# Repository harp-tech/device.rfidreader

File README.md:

# Harp RFID reader

RFID reader for 125KHz carriers.
Compible with glass capsules, buttons and cards (check pics folder).

# Licensing

The code, designs, documentation, and photos available in this repository is free: you can redistribute it and/or modify it under the terms of the used license.
Each subdirectory will contain a license or, possibly, a set of licenses if it involves both hardware and software. Check files named LICENSE.

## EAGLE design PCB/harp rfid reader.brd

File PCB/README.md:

# Harp RFID reader

## Licensing

The designs, documentation, and photos available in this repository are free: you can redistribute it and/or modify it under the terms of the used license.
Check file named LICENSE.

Copyright Filipe Carvalho 2021-2022

<br />This work is licensed under a <a rel="license" href="http://creativecommons.org/licenses/by-nc-sa/3.0/igo/">Creative Commons Attribution-NonCommercial-ShareAlike 3.0 IGO License</a>.

If your are interested in obtaining a license to sell this device, please contact filipe@open-ephys.org

[1]: https://docs.google.com/spreadsheets/d/1aobmmEzBDethzIlrm1eg0eYkBqlyX3s9WbA9KgRwVQI/edit?usp=sharing

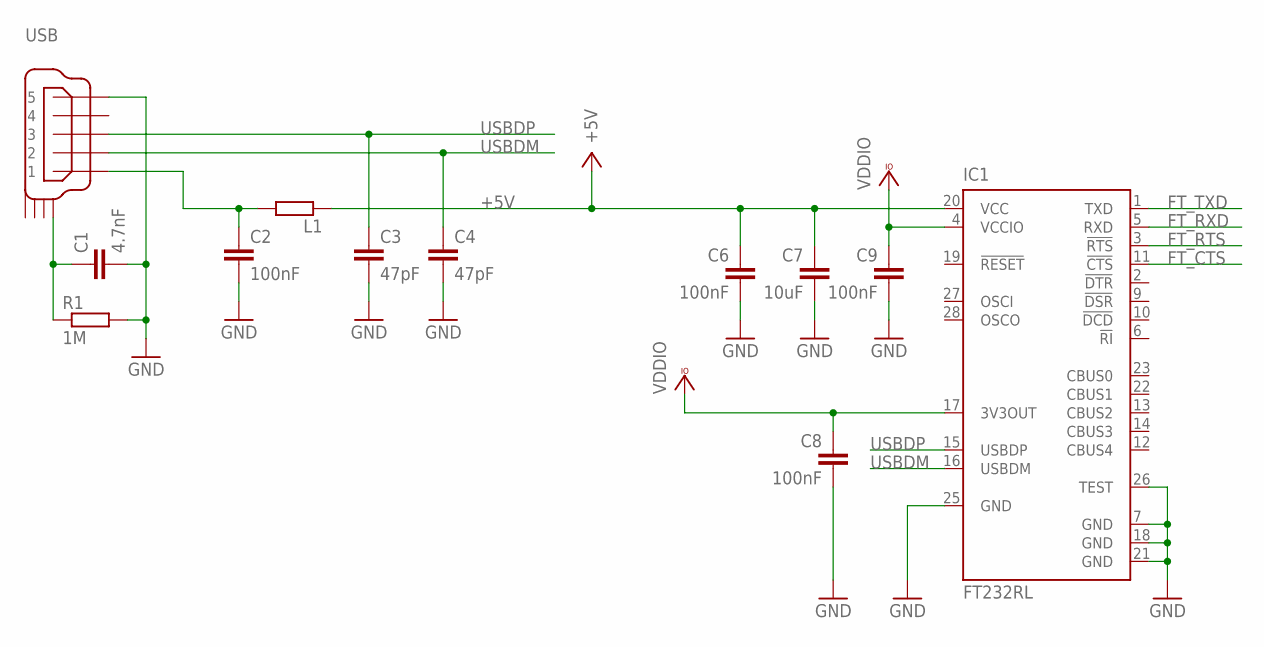
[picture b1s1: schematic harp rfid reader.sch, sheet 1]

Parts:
C1: 4.7nF; C0402
C2, C6, C8, C9: 100nF; C0402
C3, C4: 47pF; C0402
C7: 10uF; C0603
IC1: FT232RL; SSOP28
L1: ???; R0805
R1: 1M; R0402
USB: USB_MINI_B; 240-0002-1

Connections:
+5V: C6.1, C7.1, IC1.20 (VCC), L1.1; also elsewhere on the board
FT_CTS: IC1.11 (!CTS); also elsewhere on the board
FT_RTS: IC1.3 (!RTS); also elsewhere on the board
FT_RXD: IC1.5 (RXD); also elsewhere on the board
FT_TXD: IC1.1 (TXD); also elsewhere on the board
GND: C1.2, C2.2, C3.2, C4.2, C6.2, C7.2, C8.2, C9.2, IC1.7 (GND), IC1.18 (GND), IC1.21 (GND), IC1.25 (GND), IC1.26 (TEST), R1.2, USB.P$5 (5); also elsewhere on the board
unnamed: C1.1, R1.1, USB.SHIELD_1
unnamed: C2.1, L1.2, USB.P$1 (1)
USBDM: C4.1, IC1.16 (USBDM), USB.P$2 (2)
USBDP: C3.1, IC1.15 (USBDP), USB.P$3 (3)
VCCIO: C8.1, C9.1, IC1.4 (VCCIO), IC1.17 (3V3OUT); also elsewhere on the board

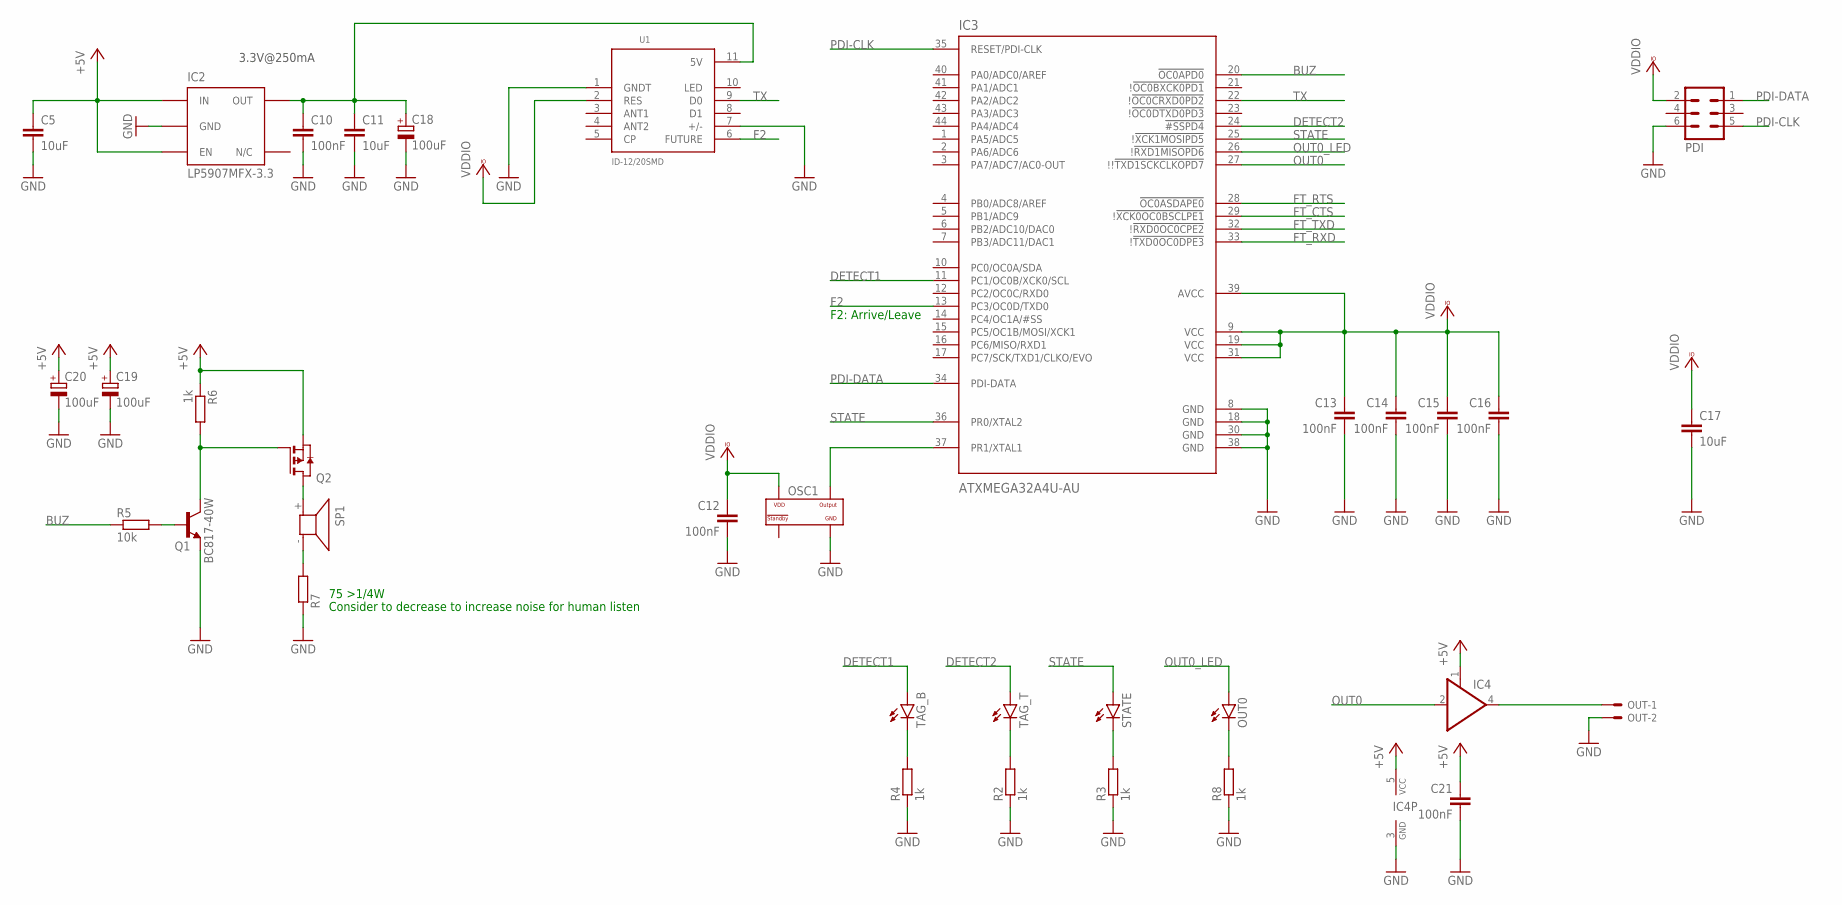
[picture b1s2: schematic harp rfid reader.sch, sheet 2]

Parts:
C5, C11, C17: 10uF; C0603
C10, C12, C13, C14, C15, C16, C21: 100nF; C0402
C18, C19, C20: 100uF; CT3216
IC2: LP5907MFX-3.3; TSOT23-5
IC3: ATXMEGA32A4U-AU; QFP80P1200X1200X120-44N
IC4: 74AHC1G126DBV; SOT23-5
OSC1: CNP-MISCELLANEOUS_OSCILLATOR; CNP-MISCELLANEOUS_OSCILLATOR_3.2X2.5
OUT: 22-23-2021
OUT0: LEDCHIP-LED0603; CHIP-LED0603
PDI: MA03-2
Q1: BC817-40W; SOT323-BEC
Q2: PMOSSOT223; SOT223
R2, R3, R4, R6, R8: 1k; R0402
R5: 10k; R0402
R7: 75 >1/4W; R0402
SP1: BUZZER-COIL_SMT-0540-S-R
STATE: LEDCHIP-LED0603; CHIP-LED0603
TAG_B: LEDCHIP-LED0603; CHIP-LED0603
TAG_T: LEDCHIP-LED0603; CHIP-LED0603
U1: ID-12/20SMD; ID-12_SMD

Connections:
+5V: C5.1, C19.+, C20.+, C21.1, IC2.1 (IN), IC2.3 (EN), IC4.1 (OE), IC4.5 (VCC), Q2.3 (S), R6.1; also elsewhere on the board
BUZ: IC3.20 (!OC0APD0), R5.1
BUZ_T: Q2.2 (D), Q2.4 (D), SP1.+
DETECT1: IC3.11 (PC1/OC0B/XCK0/SCL), TAG_B.A
DETECT2: IC3.24 (!#SSPD4), TAG_T.A
F2: IC3.13 (PC3/OC0D/TXD0), U1.6 (FUTURE)
FT_CTS: IC3.29 (!!XCK0OC0BSCLPE1); also elsewhere on the board
FT_RTS: IC3.28 (!OC0ASDAPE0); also elsewhere on the board
FT_RXD: IC3.33 (!!TXD0OC0DPE3); also elsewhere on the board
FT_TXD: IC3.32 (!!RXD0OC0CPE2); also elsewhere on the board
GND: C5.2, C10.2, C11.2, C12.2, C13.2, C14.2, C15.2, C16.2, C17.2, C18.-, C19.-, C20.-, C21.2, IC2.2 (GND), IC3.8 (GND), IC3.18 (GND), IC3.30 (GND), IC3.38 (GND), IC4.3 (GND), OSC1.P$2 (GND), OUT.2, PDI.6, Q1.E, R2.1, R3.1, R4.1, R7.1, R8.1, U1.1 (GNDT), U1.7 (+/-); also elsewhere on the board
unnamed: C10.1, C11.1, C18.+, IC2.5 (OUT), U1.11 (5V)
unnamed: R3.2, STATE.C
unnamed: R4.2, TAG_B.C
unnamed: R2.2, TAG_T.C
unnamed: OUT0.C, R8.2
unnamed: IC4.4 (O), OUT.1
unnamed: R7.2, SP1.-
unnamed: Q1.C, Q2.1 (G), R6.2
unnamed: Q1.B, R5.2
OSC1: IC3.37 (PR1/XTAL1), OSC1.P$3 (OUTPUT)
OUT0: IC3.27 (!!!TXD1SCKCLKOPD7), IC4.2 (I)
OUT0_LED: IC3.26 (!!RXD1MISOPD6), OUT0.A
PDI-CLK: IC3.35 (RESET/PDI-CLK), PDI.5
PDI-DATA: IC3.34 (PDI-DATA), PDI.1
STATE: IC3.25 (!!XCK1MOSIPD5), IC3.36 (PR0/XTAL2), STATE.A
TX: IC3.22 (!!OC0CRXD0PD2), U1.9 (D0)
VCCIO: C12.1, C13.1, C14.1, C15.1, C16.1, C17.1, IC3.9 (VCC), IC3.19 (VCC), IC3.31 (VCC), IC3.39 (AVCC), OSC1.P$4 (VDD), PDI.2, U1.2 (RES); also elsewhere on the board

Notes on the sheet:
3.3V@250mA
75 >1/4W
Consider to decrease to increase noise for human listen
F2: Arrive/Leave

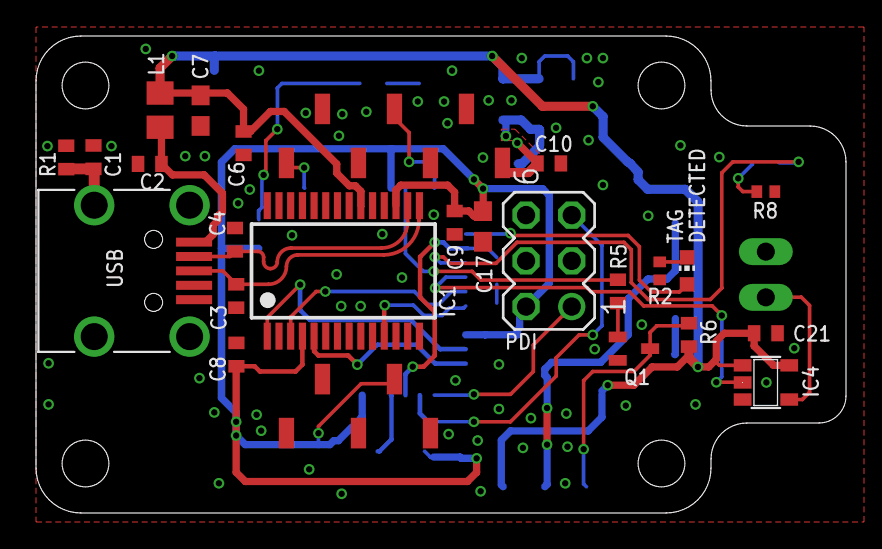
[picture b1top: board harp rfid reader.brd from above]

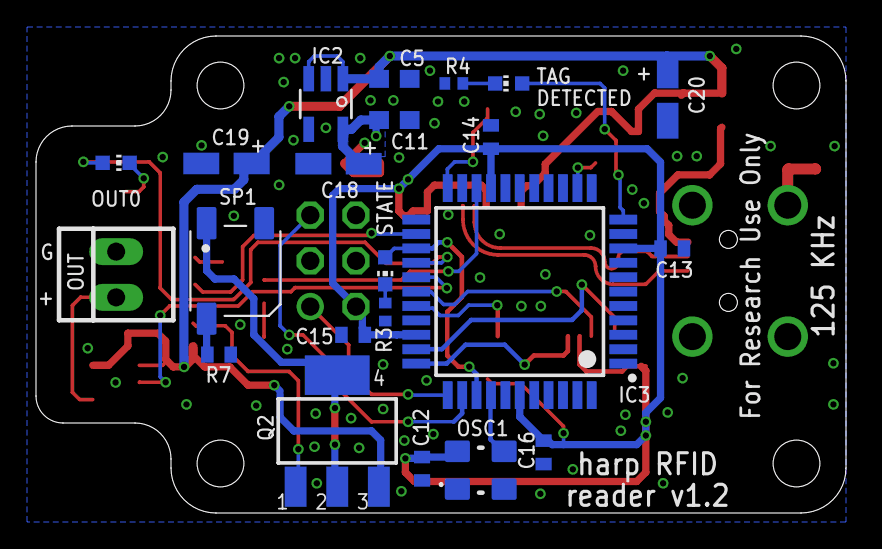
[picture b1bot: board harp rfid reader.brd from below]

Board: 2 copper layers, 45.0 x 26.5 mm, 46 parts (22 on the bottom side), 32 nets.

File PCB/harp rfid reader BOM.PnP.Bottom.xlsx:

C11 | 25.09 | 21.83 | 0 | 10uF | C0603
C12 | 23.55 | 2.46 | 270 | 100nF | C0402
C13 | 9.65 | 14.7 | 0 | 100nF | C0402
C14 | 19.72 | 20.88 | 90 | 100nF | C0402
C15 | 27.38 | 9.9 | 180 | 100nF | C0402
C16 | 16.8 | 3.37 | 270 | 100nF | C0402
C18 | 28.19 | 19.41 | 180 | 100uF | CT3216
C19 | 34.42 | 19.420000000000002 | 180 | 100uF | CT3216
C20 | 9.91 | 23.19 | 270 | 100uF | CT3216
C5 | 25.09 | 24.12 | 0 | 10uF | C0603
IC2 | 28.9 | 22.72 | 180 | LP5907MFX-3.3 | TSOT23-5
IC3 | 18.12 | 12.3 | 180 | ATXMEGA32A4U-AU | QFP80P1200X1200X120-44N
OSC1 | 20.29 | 2.38 | 0 | CNP-MISCELLANEOUS_OSCILLATOR | CNP-MISCELLANEOUS_OSCILLATOR_3.2X2.5
OUT0 | 40.549999999999997 | 19.45 | 270 |  | CHIP-LED0603
Q2 | 28.27 | 4.5599999999999996 | 0 |  | SOT223
R3 | 25.6 | 11.16 | 90 | 1k | R0402
R4 | 21.79 | 23.86 | 0 | 1k | R0402
R7 | 34.83 | 8.8000000000000007 | 180 | 75 >1/4W | R0402
SP1 | 33.92 | 13.45 | 0 | BUZZER-COIL_SMT-0540-S-R | BUZZER-COIL_SMT-0540-S-R
STATE | 25.6 | 13.45 | 180 |  | CHIP-LED0603
TAG_B | 18.739999999999998 | 23.86 | 90 |  | CHIP-LED0603

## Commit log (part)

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2021-02-19 Created README.md
2021-02-19 Added first PCB files.
2021-02-19 Added compatible devices.
2021-02-21 Added first firmware files.
2021-02-21 Increased oscillator and buzzer pads.
2021-02-21 Replaced microcontroller.
2021-02-26 Updated firmware.
2021-02-26 Correct footprints of buzzer and oscillator.
2021-02-26 Added the bootloader for ATXMEGA32A4U.
2021-05-03 Minor PCB corrections.
2021-05-03 Added 3 new capacitors.
2022-05-06 Corrected STATE and DETECT lines and increased LED resistors.
2022-05-06 Remapped TOP LED to PC1.
2022-05-08 Added new event and renamed reserved registers.
    New event: (REG 33 U64) TAG_ID_LEAVED -> When tag leaves the detection zone.
2022-05-08 Increased harp core version and changed microcontroller.
    Increased harp core to version 1.9 and changed microcontroller to ATXMEGA32A4U.
2022-05-09 Increased hardware version to match the current PCB version.
2022-05-25 Added a digital output.
2022-09-13 Added fabrication files and updated BOM.
2022-09-13 Added mechanical dimensions.
2022-09-13 Export mechanical dimensions.
2022-09-13 Added more details to mechanical dimensions file.
2022-09-13 Minor BOM correction.
2022-11-03 Minor corrections.
2022-11-07 Released firmware version 0.1.
2022-12-07 Added new registers to handle the digital output.
2022-12-07 Added routines to handle the digital output.
2022-12-07 Updated default timing.
2022-12-07 Ability to turn LEDs off.
2022-12-07 Increased firmware version to 0.2.
2022-12-07 Deleted .hex files from the repository.
2022-12-27 Removed unnecessary files.
2022-12-27 Refactored hardware files.
2022-12-27 Added .gitignore to individual folders.
2022-12-27 Renamed pics folder to Assets.
2022-12-27 Renamed files.
2022-12-28 Updated to atxmega core version 1.12.
    Also leave the default timestamp offset configured to 3 (1.5 ms).
2022-12-28 Increased firmware version to 1.0
2023-03-10 Added antenna datasheets.
2023-04-18 Add interface generators
2023-04-18 Add first draft of device schema
2023-04-18 Add automatically generated bonsai interface
2023-04-19 Change device name
2023-04-20 Favor "PulseWidth" over "PulseDuration"
2023-04-21 Fixed bad bitmasks.
    The notification and trigger bitmasks where corrected.
2023-04-22 Update schema bitMasks according to #2
2023-04-24 Reduce verbosity
2023-06-02 Improve schema readability
2023-06-02 Update `Device` classes to new schema
2023-07-05 Increased firmware version to 1.1.
2023-07-05 Added ability to also read the ISO11785 tags.
2023-08-10 Add minor clarifications to device schema
2023-08-10 Update interface to use latest generators
2023-08-10 Add interface license and package stable version
2023-08-10 Updated firmware version.
2023-08-10 Updated harp core to 1.13.
2023-09-04 Added excel file explaining how to parse the ID.
2023-09-06 Increase firmware version.
2023-09-06 Reversed ID bits and apply calculation.
2024-01-25 Increased firmware version to 1.3.
2024-01-25 Clear tag register after the tag leaves the detection zone. Fix #7
    For the ISO 11785 the register is cleared after detection because there's no indication of when the tag leaves.
2024-01-26 Increased firmware version to 1.3
2025-06-12 Create basic CI/CD for interface package
2025-06-27 First Makefile.
    Trying to create a Makefile.
    Apparently, it compiles well.
    I haven't tried sending the .hex to a device yet.
2025-10-22 Updated to atxmega core 1.15
